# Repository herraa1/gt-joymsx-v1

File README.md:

# MSX Joystick to Gigatron TTL microcomputer Joystick adapter (gt-joymsx) v1

Connect [MSX Joysticks](https://www.msx.org/wiki/Joystick/joypad_controller) to the [Gigatron TTL microcomputer](https://gigatron.io/).

> [!NOTE]
>
> No build instructions are yet provided, but if you are brave enough go for the [recommended build](#recommended-build).
>

## Introduction

The gt-joymsx v1 is an adapter that allows connecting MSX joysticks to the Gigatron TTL microcomputer.

The main features of the gt-joymsx v1 adapter are:
* small footprint
* made of widely available electronic components
* behaves as a cord extension between the Gigatron TTL microcomputer and the MSX joystick
* uses an extension cable with a female DE9 connector on the adapter's Gigatron TTL microcomputer joystick side
* uses a male DE9 PCB connector on the adapter's MSX joystick side
* no need for external power supply, the adapter draws current from the Gigatron TTL microcomputer joystick port
* super low power consumption

## [Hardware](hardware/kicad/)

The Gigatron TTL microcomputer uses [9-pin Famiclone compatible joysticks](https://www.nesdev.org/wiki/Controller_port_pinout). Those joysticks use a [Texas Instruments 4021 or compatible](https://www.ti.com/lit/ds/symlink/cd4021b.pdf) to latch and serialize the information about the pressed joystick buttons and arrows.

The [standard MSX joysticks](https://www.msx.org/wiki/Joystick/joypad_controller) are completely passive and have parallel signals for each of the buttons and arrows. The MSX computers pull up by default the signals when a MSX joystick is connected, and the MSX joysticks pull the signals to the OUT signal (pin8) when buttons or arrows are pressed (see page 27 of [MSX Technical Data Book](https://map.grauw.nl/resources/system/msxtech.pdf) for a schematic).

The gt-joymsx v1 adapter uses a CD4021BM integrated circuit to convert the signals from the MSX joystick buttons and arrows to the 9-pin Famiclone expected signalling.
As the MSX joysticks lack the `SELECT` and `START`buttons of the Famiclone joysticks, the gt-joymsx v1 adapter itself also provides two Cherry-compatible key switches to add those two buttons.

A two-sided printed circuit board (PCB) is used to put together all components:
* An angled Sega DE9 PCB male connector is used to directly connect the MSX joystick
* A PH2.0 connector is used to connect the Gigatron TTL microcomputer joystick cable extension
* Two Cherry-compatible key switches to implement the `SELECT` and `START` buttons
* the CD4021BM CMOS 8-Stage Static Shift Register
* A pair of pull-up resistor networks to provide default signals for buttons and arrows

Connection to the Gigatron TTL microcomputer joystick port is implemented using a DE9 joystick extension cable with a female DE9 connector on one side and a loose end on the other side.
The joystick extension cable loose end is wired according to the following pinout mapping.

|  |
|:--|
| Gigatron TTL microcomputer joystick connector pinout, from adapter extension cable plug side |

| Gigatron side pin | Cable color (may vary) | Signal         |
| ----------------- | ---------------------- | -------------- |
| 1                 | Red                    | unconnected    |
| 2                 | Black                  | SER_DATA/D0    |
| 3                 | Grey                   | SER_LATCH/OUT0 |
| 4                 | Orange                 | SER_PULSE/CLK  |
| 5                 | Brown                  | unconnected    |
| 6                 | Green                  | +5V            |
| 7                 | White                  | unconnected    |
| 8                 | Blue                   | GND            |
| 9                 | Yellow                 | unconnected    |

| MSX side pin | Signal |
| ------------ | ------ |
| 1            | UP     |
| 2            | DOWN   |
| 3            | LEFT   |
| 4            | RIGHT  |
| 5            | +5v    |
| 6            | TRIGA  |
| 7            | TRIGB  |
| 8            | GND    |
| 9            | GND    |

### Recommended Build

Please, use [gt-joymsx-v1 Build1](#build1) for making boards.

### [Build1](hardware/kicad/gt-joymsx-v1-build1)

[Bill Of Materials (BoM)](https://htmlpreview.github.io/?https://raw.githubusercontent.com/herraa1/gt-joymsx-v1/main/hardware/kicad/gt-joymsx-v1-build1/bom/ibom.html)

This board has been successfully built and works fine.

## [Enclosure](enclosure/)

A simple acrylic enclosure design for the project is provided to protect the electronic components and provide strain relief for the extension cord.

The enclosure uses a 5mm acrylic sheet.

## Tips

* By using this adapter in combination with a [msx-joyblue](https://github.com/herraa1/msx-joyblue-v2) adapter you can play games on the Gigatron TTL microcomputer using bluetooth adapters (for example, you can play _Racer_ using a Nintendo Wii Remote with a Wheel)

## References

Gigatron TTL microcomputer
- https://gigatron.io

MSX general purpose I/O port
* https://www.msx.org/wiki/General_Purpose_port

Famiclone pinout
- https://www.nesdev.org/wiki/Controller_port_pinout

4021 pinout
* https://www.nesdev.org/wiki/4021

## Image Sources

* https://www.oshwa.org/open-source-hardware-logo/
* https://en.wikipedia.org/wiki/File:Numbered_DE9_Diagram.svg

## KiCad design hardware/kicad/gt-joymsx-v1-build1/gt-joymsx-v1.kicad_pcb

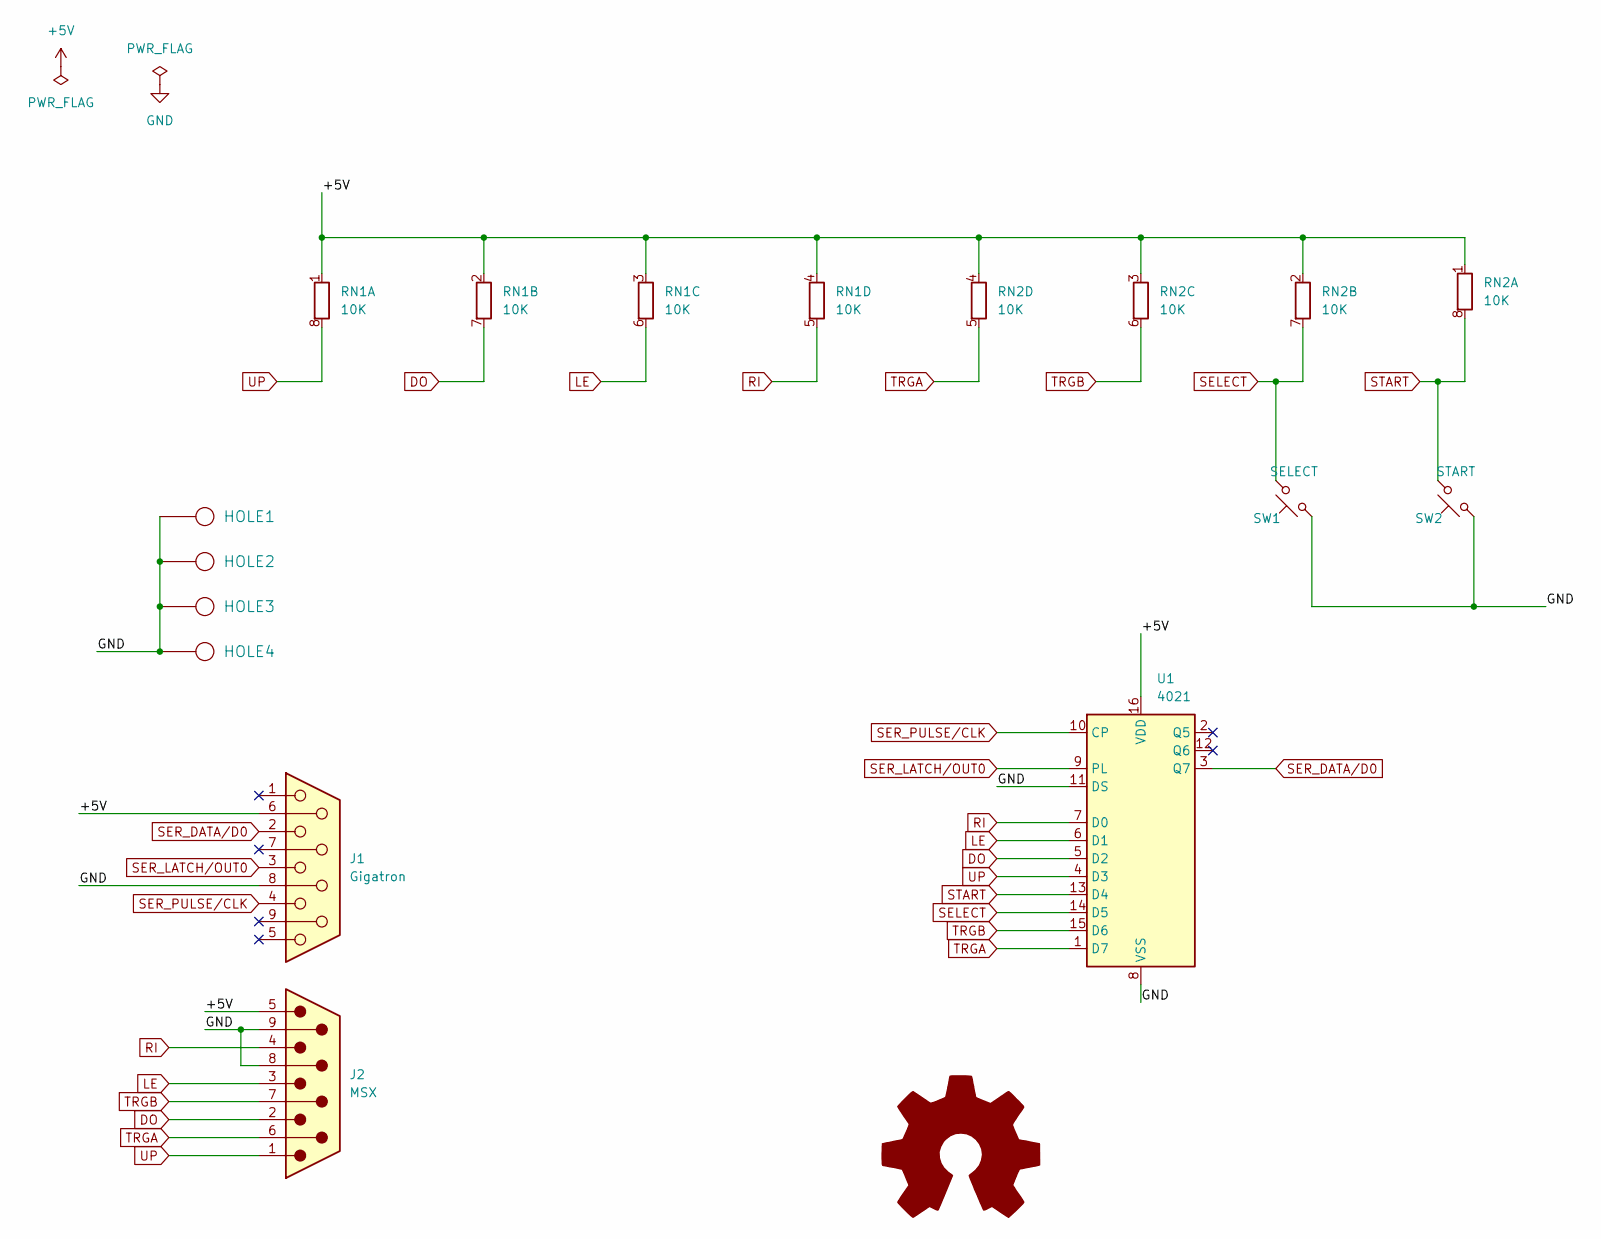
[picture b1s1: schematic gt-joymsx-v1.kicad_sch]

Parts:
HOLE1, HOLE2, HOLE3, HOLE4: HOLE; Hole_3mm
J1: Gigatron; JST_PH_S9B-PH-K_1x09_P2.00mm_Horizontal
J2: MSX; Sega-DE9_Male_Horizontal_P2.77x2.84mm_EdgePinOffset9.40mm
RN1, RN2: 10K; R_Array_Concave_4x0603
SW1: SELECT; SW_Cherry_MX_PCB_1.00u
SW2: START; SW_Cherry_MX_PCB_1.00u
SYM1: Logo_Open_Hardware_Large; OSHW-Logo_7.5x8mm_SilkScreen
U1: 4021; SOIC-16_3.9x9.9mm_P1.27mm

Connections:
+5V: J1.6, J2.5, RN1.1 (R1.1), RN1.2 (R2.1), RN1.3 (R3.1), RN1.4 (R4.1), RN2.1 (R1.1), RN2.2 (R2.1), RN2.3 (R3.1), RN2.4 (R4.1), U1.16 (VDD)
DO: J2.2, RN1.7 (R2.2), U1.5 (D2)
GND: HOLE1.1, HOLE2.1, HOLE3.1, HOLE4.1, J1.8, J2.8, J2.9, SW1.1, SW2.1, U1.8 (VSS), U1.11 (DS)
LE: J2.3, RN1.6 (R3.2), U1.6 (D1)
RI: J2.4, RN1.5 (R4.2), U1.7 (D0)
SELECT: RN2.7 (R2.2), SW1.2, U1.14 (D5)
SER_DATA/D0: J1.2, U1.3 (Q7)
SER_LATCH/OUT0: J1.3, U1.9 (PL)
SER_PULSE/CLK: J1.4, U1.10 (CP)
START: RN2.8 (R1.2), SW2.2, U1.13 (D4)
TRGA: J2.6, RN2.5 (R4.2), U1.1 (D7)
TRGB: J2.7, RN2.6 (R3.2), U1.15 (D6)
UP: J2.1, RN1.8 (R1.2), U1.4 (D3)

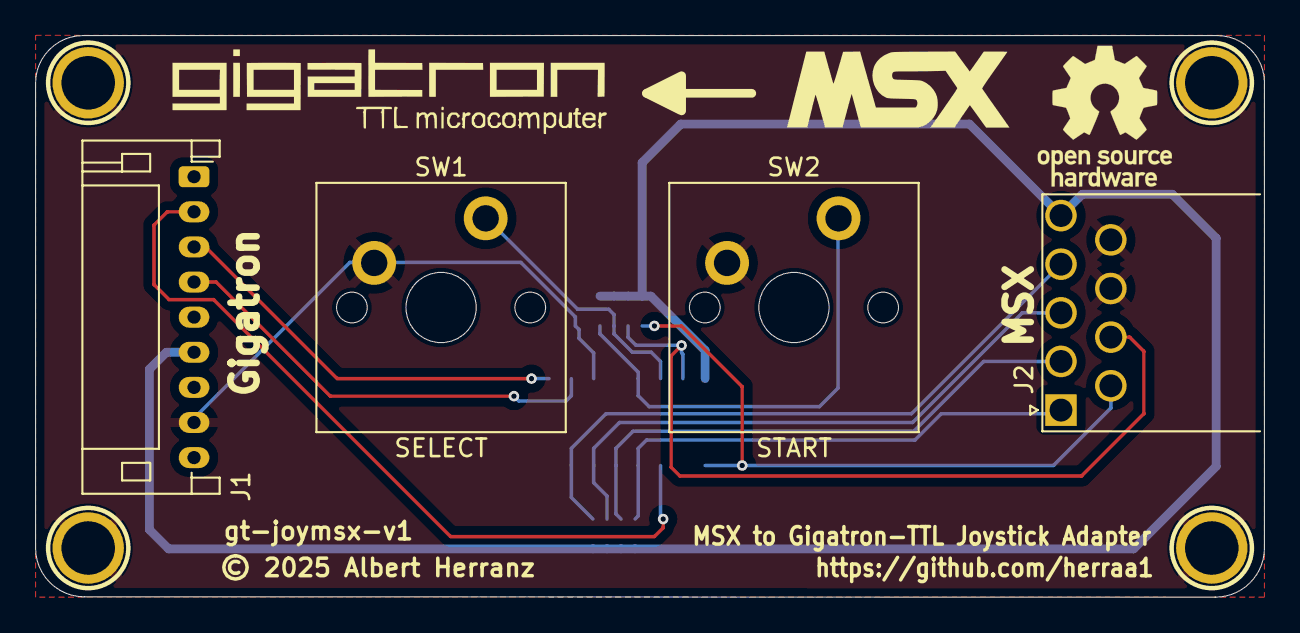
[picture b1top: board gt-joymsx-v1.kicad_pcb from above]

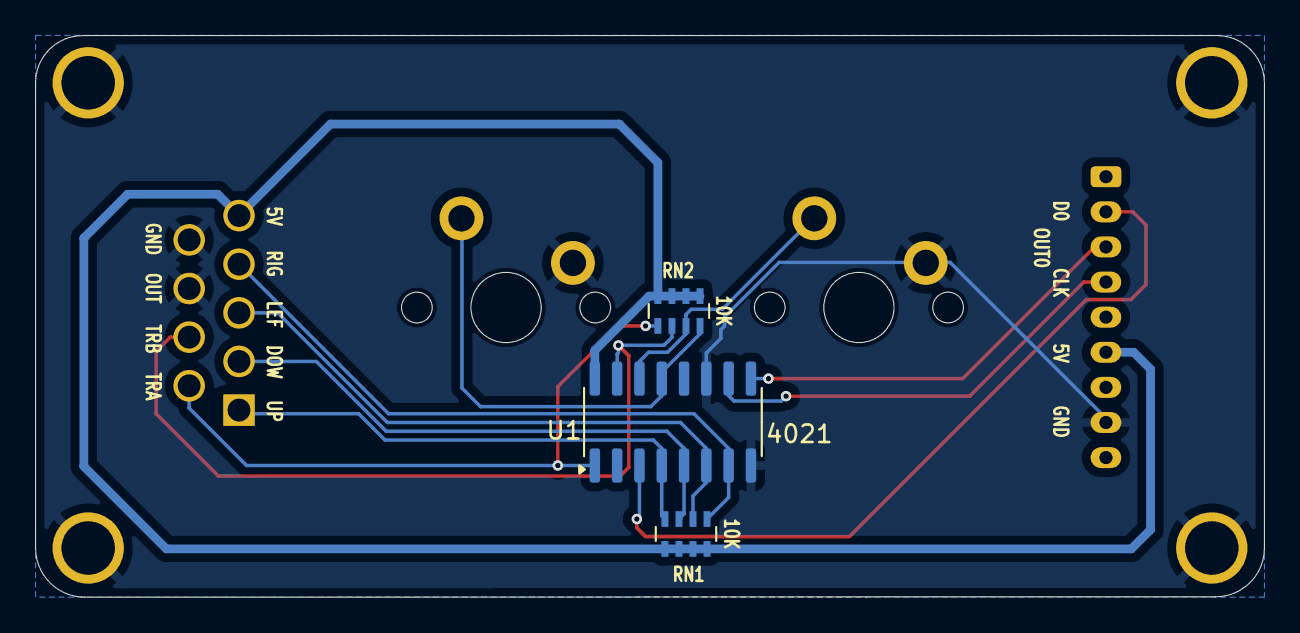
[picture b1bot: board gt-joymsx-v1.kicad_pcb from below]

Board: 2 copper layers, 70.0 x 32.0 mm, 12 parts (3 on the bottom side), 13 nets.

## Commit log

2025-06-10 Initial commit.
2025-06-14 enclosure: initial version
2026-02-27 fix htmlpreview link

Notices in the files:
hardware/kicad/gt-joymsx-v1-build1/gt-joymsx-v1.kicad_pcb:
© 2025 Albert Herranz
